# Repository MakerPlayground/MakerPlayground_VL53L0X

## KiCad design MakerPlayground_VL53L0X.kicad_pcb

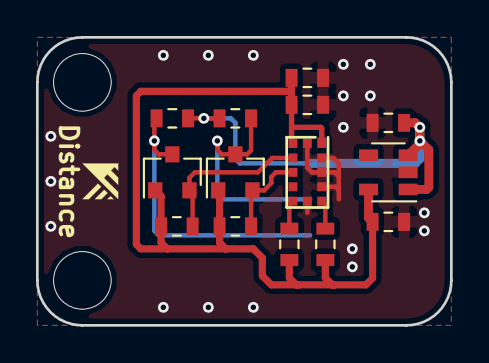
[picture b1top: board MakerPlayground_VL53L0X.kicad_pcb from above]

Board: 2 copper layers, 23.0 x 16.0 mm, 15 parts (1 on the bottom side), 9 nets.

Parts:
C1: 4.7uF; C_0603_1608Metric
C2: 0.1uF; C_0603_1608Metric
C4, C5: 1uF; C_0603_1608Metric
J1: Connector; JST_PH_S4B-PH-SM4-TB_1x04-1MP_P2.00mm_Horizontal
Q1, Q2: BSS138; SOT-23
R1, R2, R3, R4, R5, R6: 10k; R_0603_1608Metric
U1: VL53L0X
U2: AP2127K-3.3; SOT-23-5

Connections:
+3V3: C1.1, C2.1, C5.1, Q1.1, Q2.1, R1.1, R3.2, R5.2, R6.1, U1.1, U1.11, U2.5
GND: C1.2, C2.2, C4.2, C5.2, J1.1, J1.MP, U1.2, U1.3, U1.4, U1.6, U1.12, U2.2
unnamed: R1.2, U1.7
unnamed: R6.2, U1.5
SCL: J1.4, Q2.3, R4.1
SCL_S: Q2.2, R5.1, U1.10
SDA: J1.3, Q1.3, R2.1
SDA_S: Q1.2, R3.1, U1.9
VCC: C4.1, J1.2, R2.2, R4.2, U2.1, U2.3

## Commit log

2018-11-07 The first commit of MakerPlayground_VL53L0X Hexagon-shape sensor board.
2018-11-07 The first commit of MakerPlayground_VL53L0X square shape.
2018-11-07 Improve GND connectivity, new I2C signal path & PTH alignment.
